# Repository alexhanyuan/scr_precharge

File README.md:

# scr_precharge
Controller for Solid State Tesla Coil power supply precharging with SCRs. I got tired of welding relays and didn't have the room for larger (>30A) contactors. I had a bunch of Semikron SKKT dual SCR modules, which were the same Semipack 1 style diode modules I was already using. So, using this precharge controller gets rid of the main relay as well as the precharge resistor and relay.

Eagle files for Semipack 1 gate driver boards are also included. These can be soldered up for modules with either gate configuration (GK GK or GK KG). The parts for the spade connectors that work with the Semipack 1 modules are:
https://www.digikey.com/en/products/detail/keystone-electronics/3544/303877

ST Microelectronics has a good app note on controlling SCRs and topologies:
https://www.st.com/resource/en/application_note/an4606-inrushcurrent-limiter-circuits-icl-with-triacs-and-thyristors-scr-and-controlled-bridge-design-tips-stmicroelectronics.pdf

The board comprises of a zero crossing detector, an ATTINY85 which generates the appropriate PWM gate signals, GDT outputs, and opto-isolated control inputs for precharge and run modes. There are two versions of the board, only difference being the type of GDT used, depending on the type of SCR configuration (dual or half SCR/diode modules).

The SCRs will need a gate resistor sized appropriately for the amount of current necessary to turn it on. I used 5.1 ohms on the Semipack 1 SKKT modules. The precharge board outputs must also be phased properly. Additionally, on 120VAC input, the hot line must be connected to pin 1 of X2 otherwise the zero crossing detector will not be able to detect any zero crossings. With 240VAC, both lines are hot so it will not matter.

Pick your opto of choice, then size the resistors according to the logic voltage. I used this with a UD3 so the signals were 24V.

If you have any questions or are looking for a couple of bare boards, feel free to shoot me a message! 

|:--:| 
| *Figure 1. Controller board. Note that this is was the original version and modifications needed to be made to the zero crossing detector. These changes are reflected in the latest board files.* |

|:--:| 
| *Figure 2. Schematic of single output controller board.* |

|:--:| 
| *Figure 3. Dual Semikron SCR modules with the gate boards.* |

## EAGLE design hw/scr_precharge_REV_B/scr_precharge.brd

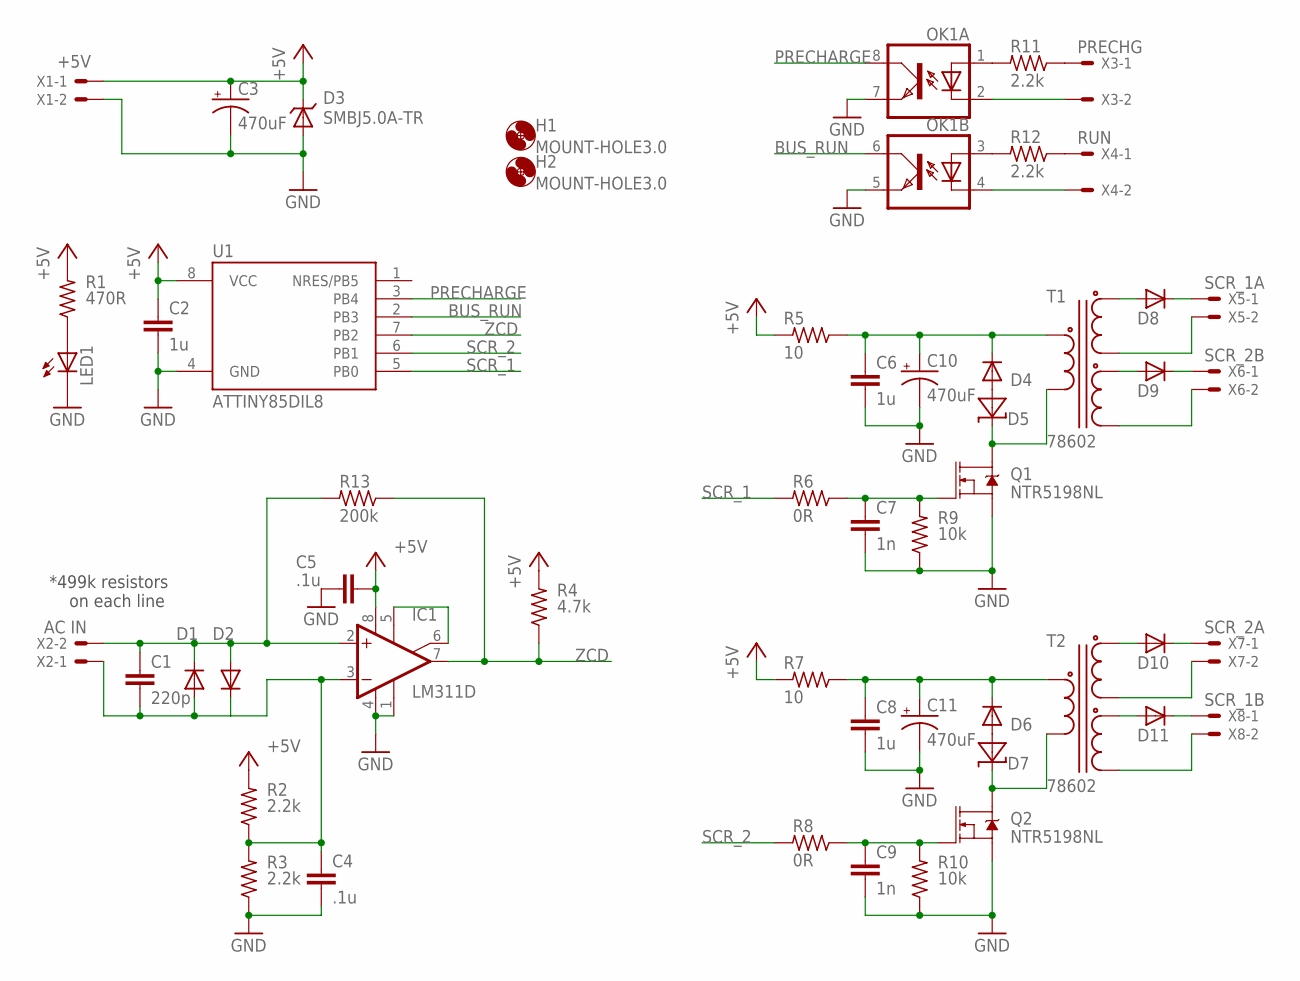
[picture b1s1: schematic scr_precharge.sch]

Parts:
C1: 220p; C0805
C2, C6, C8: 1u; C0805
C3, C10, C11: 470uF; E3,5-8
C4, C5: .1u; C0805
C7, C9: 1n; C0805
D1, D2, D4, D6, D8, D9, D10, D11: 1N4148MICROMELF; MICROMELF-W
D3: SMBJ5.0A-TR; DO214AA
D5, D7: SMAZ12-TP; DO-214AC
H1, H2: MOUNT-HOLE3.0; 3,0
IC1: LM311D; SO08
LED1: LEDCHIP-LED0805; CHIP-LED0805
OK1: ILD621; DIL08
Q1, Q2: NTR5198NL; SOT23-3
R1: 470R; R0805
R2, R3, R11, R12: 2.2k; R0805
R4: 4.7k; R0805
R5, R7: 10; R2010
R6, R8: 0R; R0805
R9, R10: 10k; R0805
R13: 200k; R0805
T1, T2: 78602; J-STD-020D
U1: ATTINY85DIL8; DIL8
X1: +5V; 22-23-2021
X2: AC IN; 22-23-2021
X3: PRECHG; 22-23-2021
X4: RUN; 22-23-2021
X5: SCR_1A; 22-23-2021
X6: SCR_2B; 22-23-2021
X7: SCR_2A; 22-23-2021
X8: SCR_1B; 22-23-2021

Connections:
+5V: C2.1, C3.+, C5.2, D3.C, IC1.8 (V+), R1.2, R2.2, R4.2, R5.2, R7.2, U1.8 (VCC), X1.1
BUS_RUN: OK1.6 (COL), U1.2 (PB3)
GND: C2.2, C3.-, C4.2, C5.1, C6.2, C7.2, C8.2, C9.2, C10.-, C11.-, D3.A, IC1.1 (GND), IC1.4 (V-), LED1.C, OK1.5 (EMIT), OK1.7 (EMIT), Q1.2 (S), Q2.2 (S), R3.1, R9.1, R10.1, U1.4 (GND), X1.2
unnamed: OK1.1 (A), R11.2
unnamed: D4.A, D5.A
unnamed: C6.1, C10.+, D4.C, R5.1, T1.P$1
unnamed: D8.A, T1.P$2
unnamed: D5.C, Q1.3 (D), T1.P$6
unnamed: D8.C, X5.1
unnamed: T1.P$5, X5.2
unnamed: T1.P$4, X6.2
unnamed: D9.C, X6.1
unnamed: D9.A, T1.P$3
unnamed: C8.1, C11.+, D6.C, R7.1, T2.P$1
unnamed: D7.C, Q2.3 (D), T2.P$6
unnamed: D6.A, D7.A
unnamed: D10.A, T2.P$2
unnamed: D10.C, X7.1
unnamed: T2.P$5, X7.2
unnamed: T2.P$4, X8.2
unnamed: D11.C, X8.1
unnamed: D11.A, T2.P$3
unnamed: C1.1, D1.C, D2.A, IC1.2 (+IN), R13.2, X2.2
unnamed: LED1.A, R1.1
unnamed: OK1.3 (A), R12.2
unnamed: R12.1, X4.1
unnamed: R11.1, X3.1
unnamed: OK1.4 (C), X4.2
unnamed: OK1.2 (C), X3.2
unnamed: C7.1, Q1.1 (G), R6.1, R9.2
unnamed: C9.1, Q2.1 (G), R8.1, R10.2
unnamed: C1.2, C4.1, D1.A, D2.C, IC1.3 (-IN), R2.1, R3.2, X2.1
unnamed: IC1.5 (ON), IC1.6 (ON/STR)
PRECHARGE: OK1.8 (COL), U1.3 (PB4)
SCR_1: R6.2, U1.5 (PB0)
SCR_2: R8.2, U1.6 (PB1)
ZCD: IC1.7 (OUT), R4.1, R13.1, U1.7 (PB2)

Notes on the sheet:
*499k resistors on each line

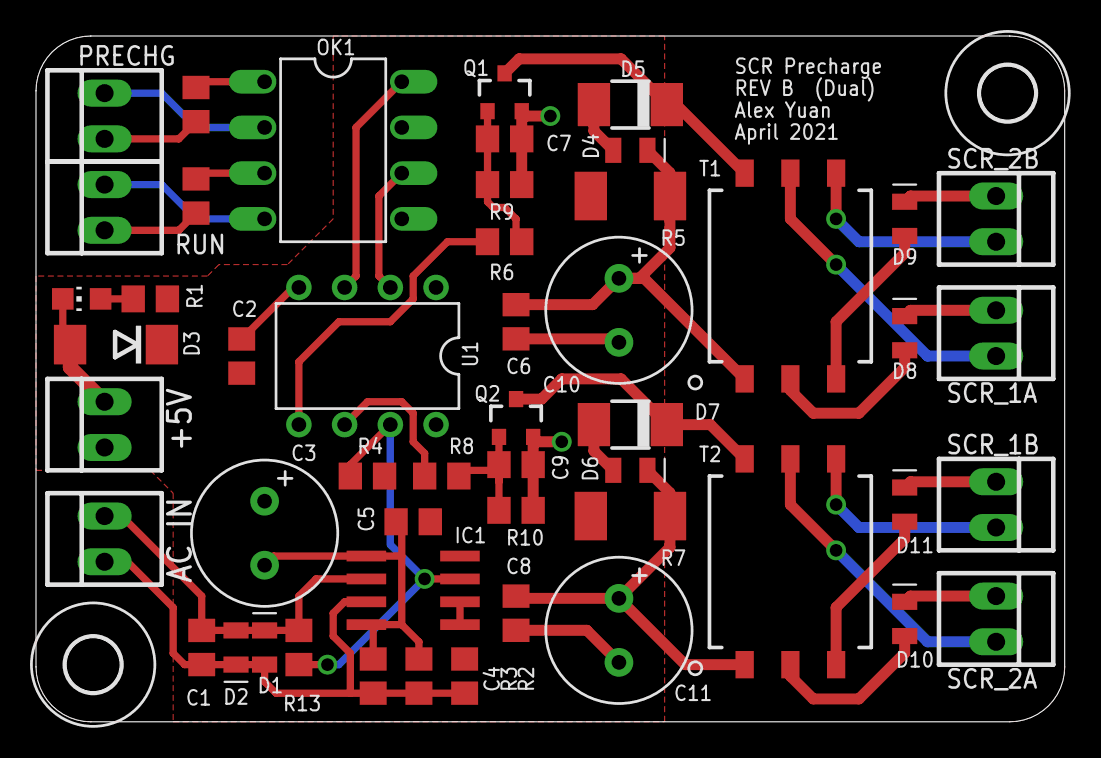
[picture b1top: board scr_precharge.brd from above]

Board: 2 copper layers, 57.1 x 38.1 mm, 53 parts (0 on the bottom side), 37 nets.

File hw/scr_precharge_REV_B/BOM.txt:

Partlist

Exported from scr_precharge.sch at 8/6/2022 15:54

EAGLE Version 7.6.0 Copyright (c) 1988-2016 CadSoft

Assembly variant: 

Part     Value           Device             Package      Library               Sheet

C1       220p            C-EUC0805          C0805        resistor              1
C2       1u              C-EUC0805          C0805        resistor              1
C3       470uF           CPOL-USE3.5-8      E3,5-8       resistor              1
C4       .1u             C-EUC0805          C0805        resistor              1
C5       .1u             C-EUC0805          C0805        resistor              1
C6       1u              C-EUC0805          C0805        resistor              1
C7       1n              C-EUC0805          C0805        resistor              1
C8       1u              C-EUC0805          C0805        resistor              1
C9       1n              C-EUC0805          C0805        resistor              1
C10      470uF           CPOL-USE3.5-8      E3,5-8       resistor              1
C11      470uF           CPOL-USE3.5-8      E3,5-8       resistor              1
D1       1N4148MICROMELF 1N4148MICROMELF    MICROMELF-W  diode                 1
D2       1N4148MICROMELF 1N4148MICROMELF    MICROMELF-W  diode                 1
D3       SMBJ5.0A-TR     SMBJ5.0A-TR        DO214AA      diode                 1
D4       1N4148MICROMELF 1N4148MICROMELF    MICROMELF-W  diode                 1
D5       SMAZ12-TP       SMAZ12-TP          DO-214AC     diode                 1
D6       1N4148MICROMELF 1N4148MICROMELF    MICROMELF-W  diode                 1
D7       SMAZ12-TP       SMAZ12-TP          DO-214AC     diode                 1
D8       1N4148MICROMELF 1N4148MICROMELF    MICROMELF-W  diode                 1
D9       1N4148MICROMELF 1N4148MICROMELF    MICROMELF-W  diode                 1
D10      1N4148MICROMELF 1N4148MICROMELF    MICROMELF-W  diode                 1
D11      1N4148MICROMELF 1N4148MICROMELF    MICROMELF-W  diode                 1
IC1      LM311D          LM311D             SO08         linear                1
LED1                     LEDCHIP-LED0805    CHIP-LED0805 led                   1
OK1      ILD621          ILD621             DIL08        optocoupler           1
Q1       SSM3K341R.LF    MOSFET-NCH-AO3404A SOT23-3      SparkFun-DiscreteSemi 1
Q2       SSM3K341R.LF    MOSFET-NCH-AO3404A SOT23-3      SparkFun-DiscreteSemi 1
R1       470R            R-US_R0805         R0805        resistor              1
R2       2.2k            R-US_R0805         R0805        resistor              1
R3       2.2k            R-US_R0805         R0805        resistor              1
R4       4.7k            R-US_R0805         R0805        resistor              1
R5       10              R-US_R2010         R2010        resistor              1
R6       0R              R-US_R0805         R0805        resistor              1
R7       10              R-US_R2010         R2010        resistor              1
R8       0R              R-US_R0805         R0805        resistor              1
R9       10k             R-US_R0805         R0805        resistor              1
R10      10k             R-US_R0805         R0805        resistor              1
R11      2.2k            R-US_R0805         R0805        resistor              1
R12      2.2k            R-US_R0805         R0805        resistor              1
R13      200k            R-US_R0805         R0805        resistor              1
T1       78602           78602              J-STD-020D   Alex                  1
T2       78602           78602              J-STD-020D   Alex                  1
U1       ATTINY85DIL8    ATTINY85DIL8       DIL8         attiny85              1
X1       +5V             22-23-2021         22-23-2021   con-molex             1
X2       AC IN           22-23-2021         22-23-2021   con-molex             1
X3       PRECHG          22-23-2021         22-23-2021   con-molex             1
X4       RUN             22-23-2021         22-23-2021   con-molex             1
X5       SCR_1A          22-23-2021         22-23-2021   con-molex             1
X6       SCR_2B          22-23-2021         22-23-2021   con-molex             1
X7       SCR_2A          22-23-2021         22-23-2021   con-molex             1
X8       SCR_1B          22-23-2021         22-23-2021   con-molex             1

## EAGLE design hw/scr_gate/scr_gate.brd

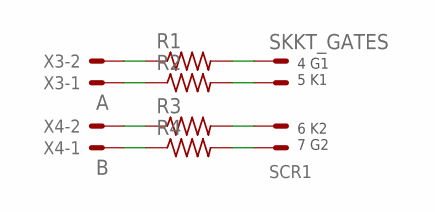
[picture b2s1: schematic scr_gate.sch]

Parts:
R1, R2, R3, R4: R-US_M0805; M0805
SCR1: SKKT_GATES
X3: A; 22-23-2021
X4: B; 22-23-2021

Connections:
unnamed: R3.2, SCR1.P$3 (3), SCR1.P$7 (3)
unnamed: R1.2, SCR1.P$1 (1), SCR1.P$5 (1)
unnamed: R2.2, SCR1.P$2 (2), SCR1.P$6 (2)
unnamed: R2.1, X3.1
unnamed: R4.2, SCR1.P$4 (4), SCR1.P$8 (4)
unnamed: R1.1, X3.2
unnamed: R4.1, X4.1
unnamed: R3.1, X4.2

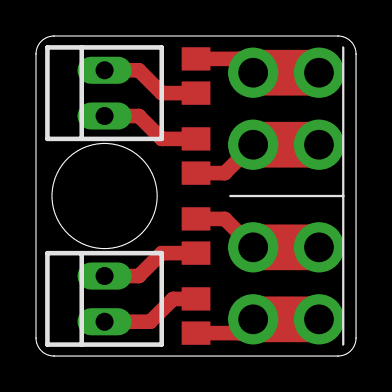
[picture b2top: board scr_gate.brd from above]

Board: 2 copper layers, 17.8 x 17.8 mm, 7 parts (0 on the bottom side), 8 nets.

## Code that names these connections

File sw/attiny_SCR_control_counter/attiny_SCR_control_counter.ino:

// SCR precharge code for attiny
// 210711
// change digitalRead and digitalWrites to direct register access in final code revision

#define precharge 4     // precharge input pin
#define bus_run   3     // bus_run input pin
#define SCR_1     0     // SCR 1 output pin
#define SCR_2     1     // SCR 2 output pin
#define timeout   123   // max TCNT1 value before it shuts off PWM outputs, this should kick in right before the next 60Hz half cycle
#define precharge_speed 3000 // adjusts precharge speed, larger = longer time, slower precharge

byte ZC = 0;            // zero crossing status
byte charge_status = 0; // 0 = off, 1 = charging, 2 = run, 3 = precharge -> run
bool bus_run_condition = 0;
bool precharge_condition = 0;
int alpha = 0;          // delay iterator

void setup(void) {
  pinMode(precharge, INPUT_PULLUP);  // precharge, active high
  pinMode(bus_run,   INPUT_PULLUP);  // run, active high
  pinMode(SCR_1, OUTPUT);    // SCR trigger 1, these probably don't need to be defined, but i'm just making sure
  pinMode(SCR_2, OUTPUT);    // SCR trigger 2
  digitalWrite(SCR_1, LOW);  // ensure digital outputs are LOW
  digitalWrite(SCR_2, LOW);  // ensure digital outputs are LOW
  
  // SCR pulsing PWM configuration
  OCR0A = 80;           // set PWM1 duty cycle (about 50µs pulse, pin 9)
  OCR0B = 80;           // set PWM2 duty cycle (about 50µs pulse, pin 10)
  TCCR0B = 0b00000001;  // set Timer1 clock to CLKio/8 (get PWM frequency of 3.9375 kHz)
  TCCR0A =  0;          // ensure SCR outputs are off
  
  // counter configuration
  TCCR1 = 0b00001010;   // CLKio/512 prescaler
  OCR1A = timeout-2;    // delay before turning on SCRs for precharge
  OCR1B = timeout;      // shut off SCRs, this is about how long a 60Hz half cycle period is, minus a slight margin
  GTCCR = 0;            // make sure everything here is disabled!!!!!!!!!!!!!!!!!
  TIMSK = 0b00100000;   // enable OCM B INT, B acts as a timeout and shuts off SCRs

  attachInterrupt(0, ZC_detect, CHANGE);  // enable INT0 for ZCD
}

void ZC_detect() { // ISR to handle zero crossing event  
  TCCR0A =  0; // turn off SCRs, though they should be off at this point already due to the timeout ISR
  
  if(digitalRead(2)) ZC = 1; // determines polarity of AC cycle
  else ZC = 2;

  TCNT0 = 0; // this reduces overal jitter of the SCR PWM
  TCNT1 = 0; // reset counter

  if(charge_status == 2) { // having this here reduces some jitter when PWM first starts in the cycle
    TCCR0A = (ZC == 1) ? 0x81 : 0x21; // enable SCRs based on AC polarity
    ZC = 0; // this for loop doesn't need to be accessed till the next 60Hz half cycle
  }
}

void loop() {
  bus_run_condition = !digitalRead(bus_run);
  precharge_condition = !digitalRead(precharge);

//  if(bus_run_condition && !precharge_condition) { // active low, if bus_run and not precharging // add && precharge_done maybe for soft transistion to run
//  if(bus_run_condition && precharge_condition && (charge_status == 1)) { // To run, UD3 enables both of these. Check that it came from precharge status.
  if(bus_run_condition && precharge_condition) {
    if(charge_status != 2) {
      charge_status = 2; // it is now in run mode
      TIMSK = TIMSK & 0b10111111; // unenable OCM A INT
    }
  }
    
  else if(!bus_run_condition && precharge_condition) { // precharging
    if(charge_status == 0) {
      charge_status = 1;    // it is now in charging mode
      OCR1A = timeout-2;    // reset charging progress
      alpha = 0;            // reset delay iterator
    }
    
    if(charge_status == 1) {
      TIMSK = TIMSK | 0b01000000; // enable OCM A INT

      if(alpha >= precharge_speed) {  // decrement OCR0A at precharge speed rate
        OCR1A -= 1;                   // turn on SCR earlier
        if(OCR1A <= 60) OCR1A = 60;   // limit earliest turn on to about 97 degrees (only needs to go to 90 degrees for max voltage)
        alpha = 0;                    // reset delay iterator
      }
      else alpha++;                   // increment delay iterator
    }
  }

  else { // neither, shut everything off                                          if(!bus_run_condition && !precharge_condition) {
    charge_status = 0;                // not trying to charge or run
    TIMSK = TIMSK & 0b10111111;       // unenable OCM A INT

//    TCCR1A =  0; // turn off everything. enabling this immediately turns off the output, disabling turns off the output on the next ZCD
  }
}

ISR(TIMER1_COMPA_vect) { // timer 1 interrupt
  if(TCNT1 > OCR1A) { // this prevents the initial full pulse before precharging, which is bad
    TCCR0A = ((ZC == 1) && (ZC != 0)) ? 0x81 : 0x21; // enable SCRs based on AC polarity  ********************** check for ZC = 2 maybe? <<kinda done
  }
}

ISR(TIMER1_COMPB_vect) { // timer 1 interrupt
  TCCR0A =  0; // timeout, shut SCRs off before start of next 60Hz half cycle
}

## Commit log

2022-08-06 adding photo of skkt gate board
2022-08-06 testing readme photo captions
2022-08-06 added more photo captions to readme
2022-08-06 added BOMs
2022-08-06 more README.md changes
2022-08-06 asdf
2022-08-07 typo fix and DNP 1n caps

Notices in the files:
parts and their libraries:
SparkFun-DiscreteSemi: Licensing: Creative Commons ShareAlike 4.0 International - https://creativecommons.org/licenses/by-sa/4.0
